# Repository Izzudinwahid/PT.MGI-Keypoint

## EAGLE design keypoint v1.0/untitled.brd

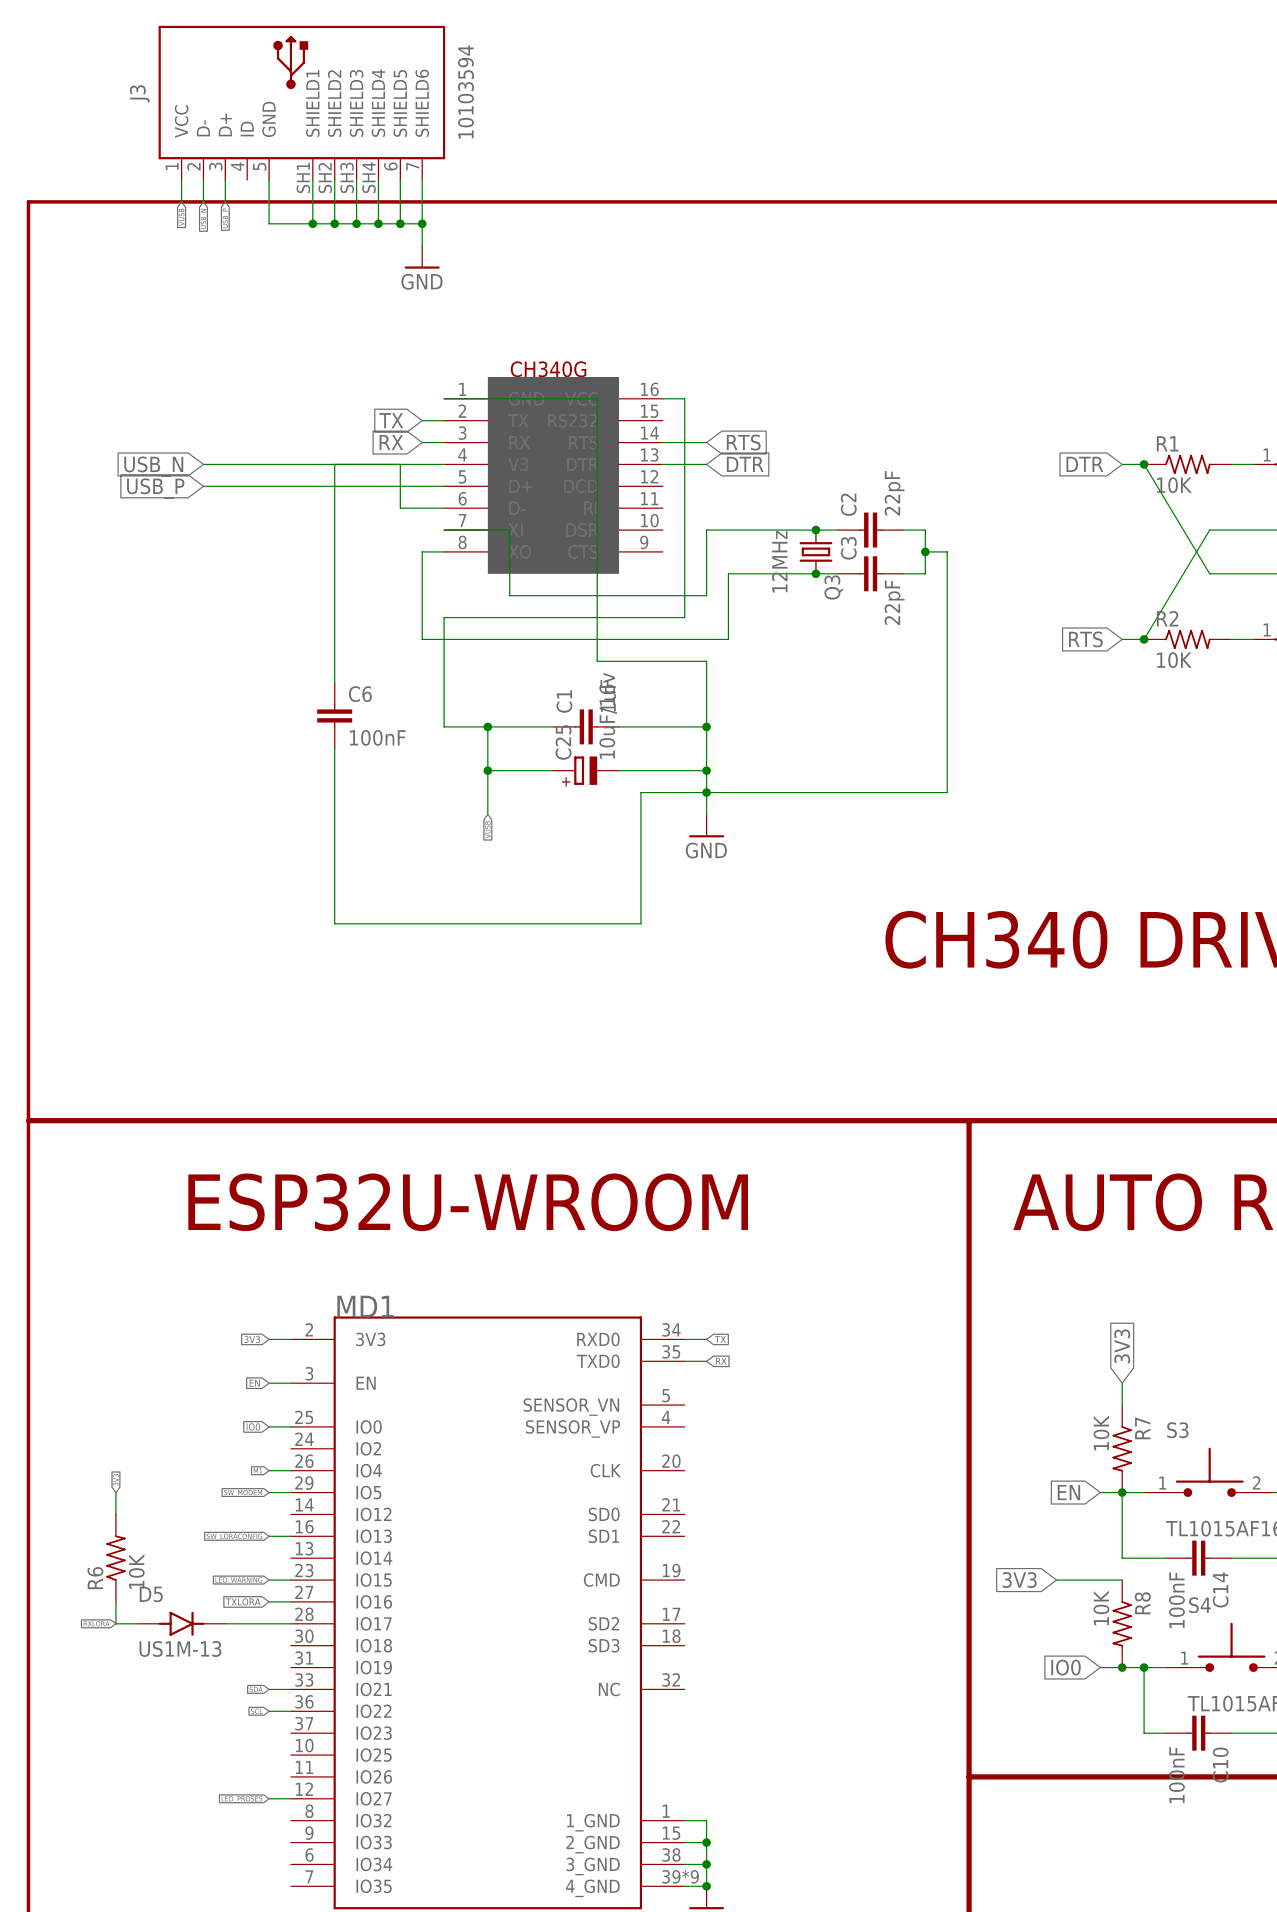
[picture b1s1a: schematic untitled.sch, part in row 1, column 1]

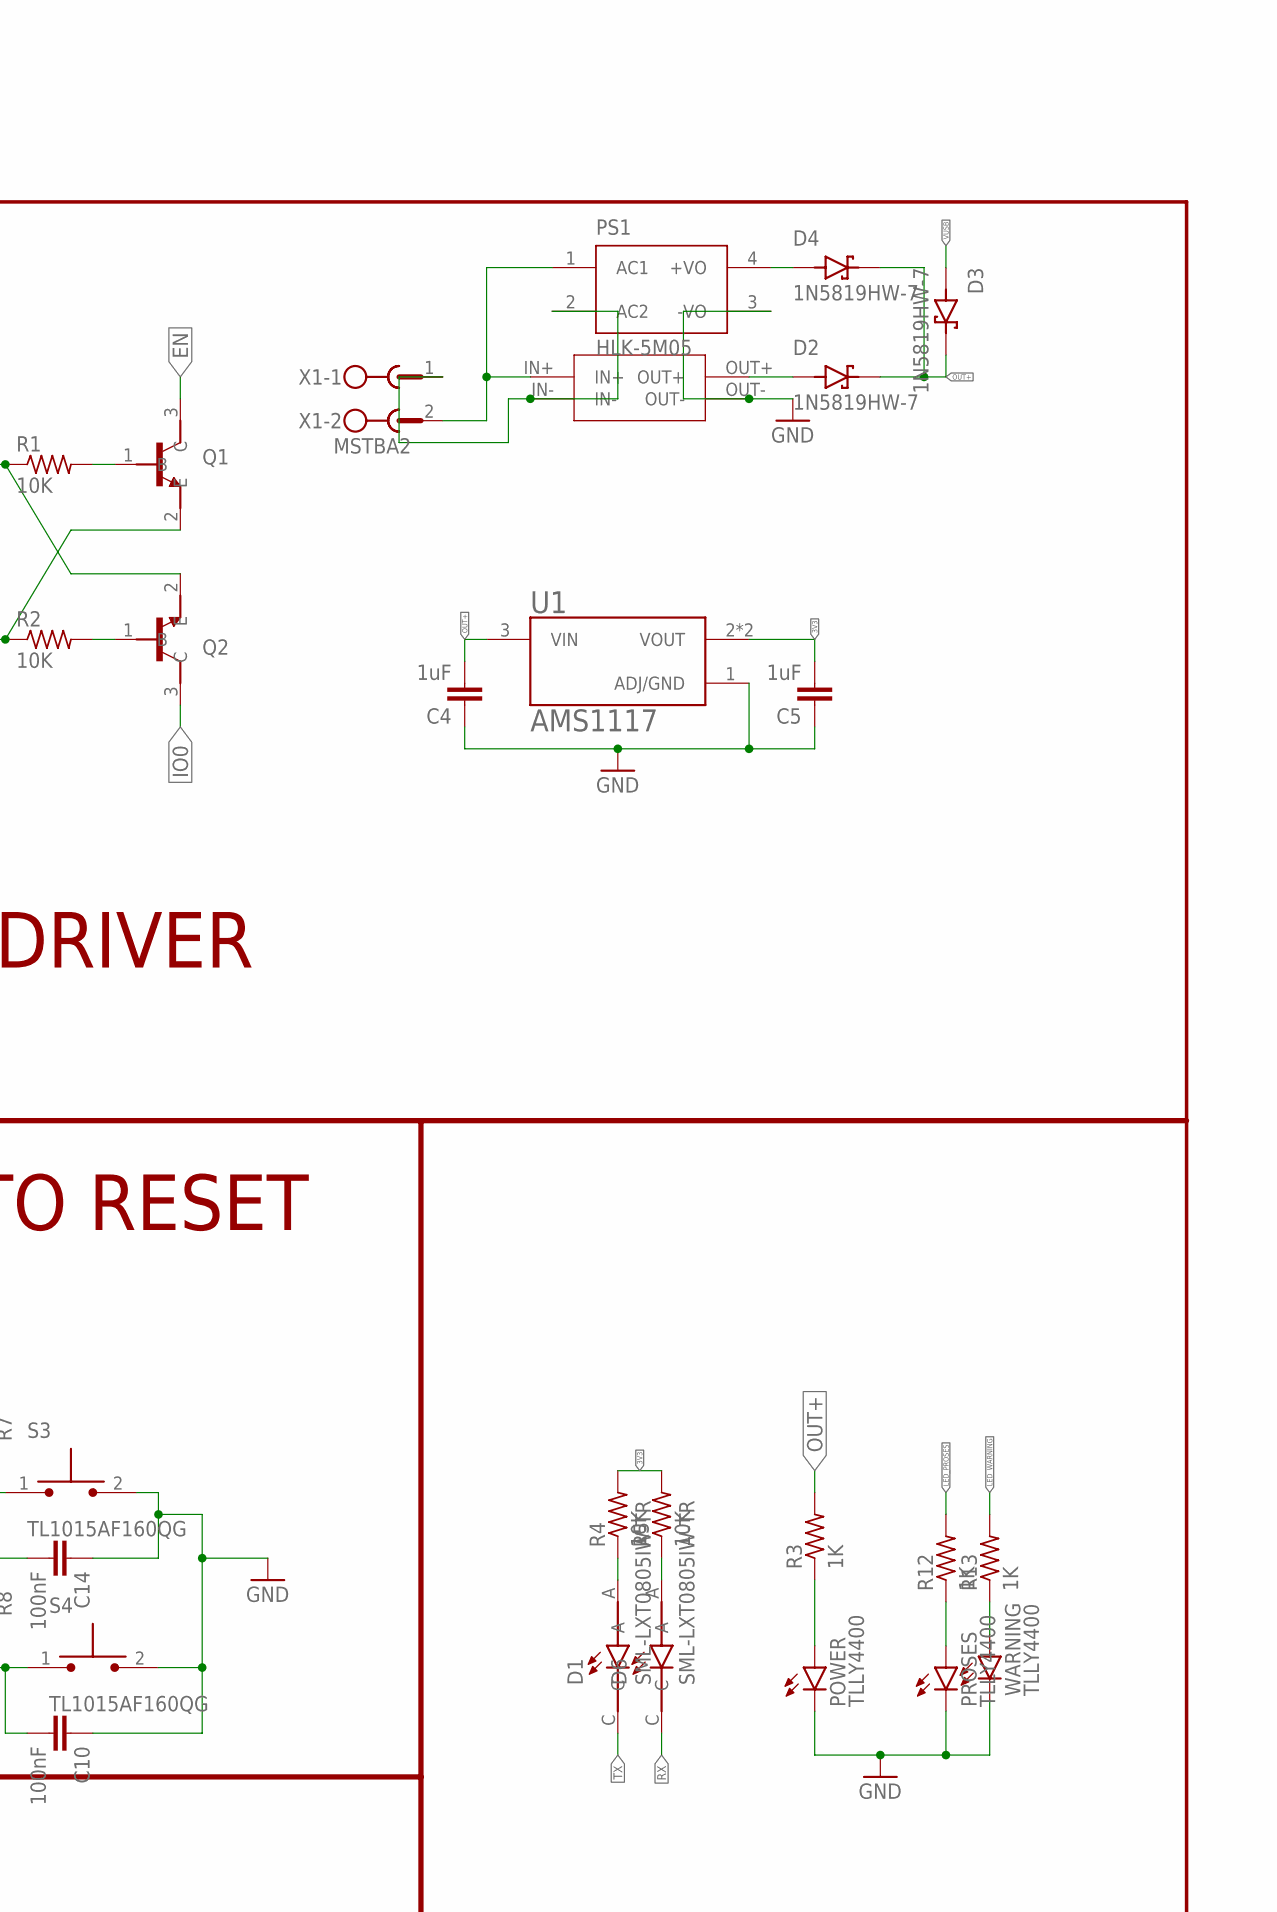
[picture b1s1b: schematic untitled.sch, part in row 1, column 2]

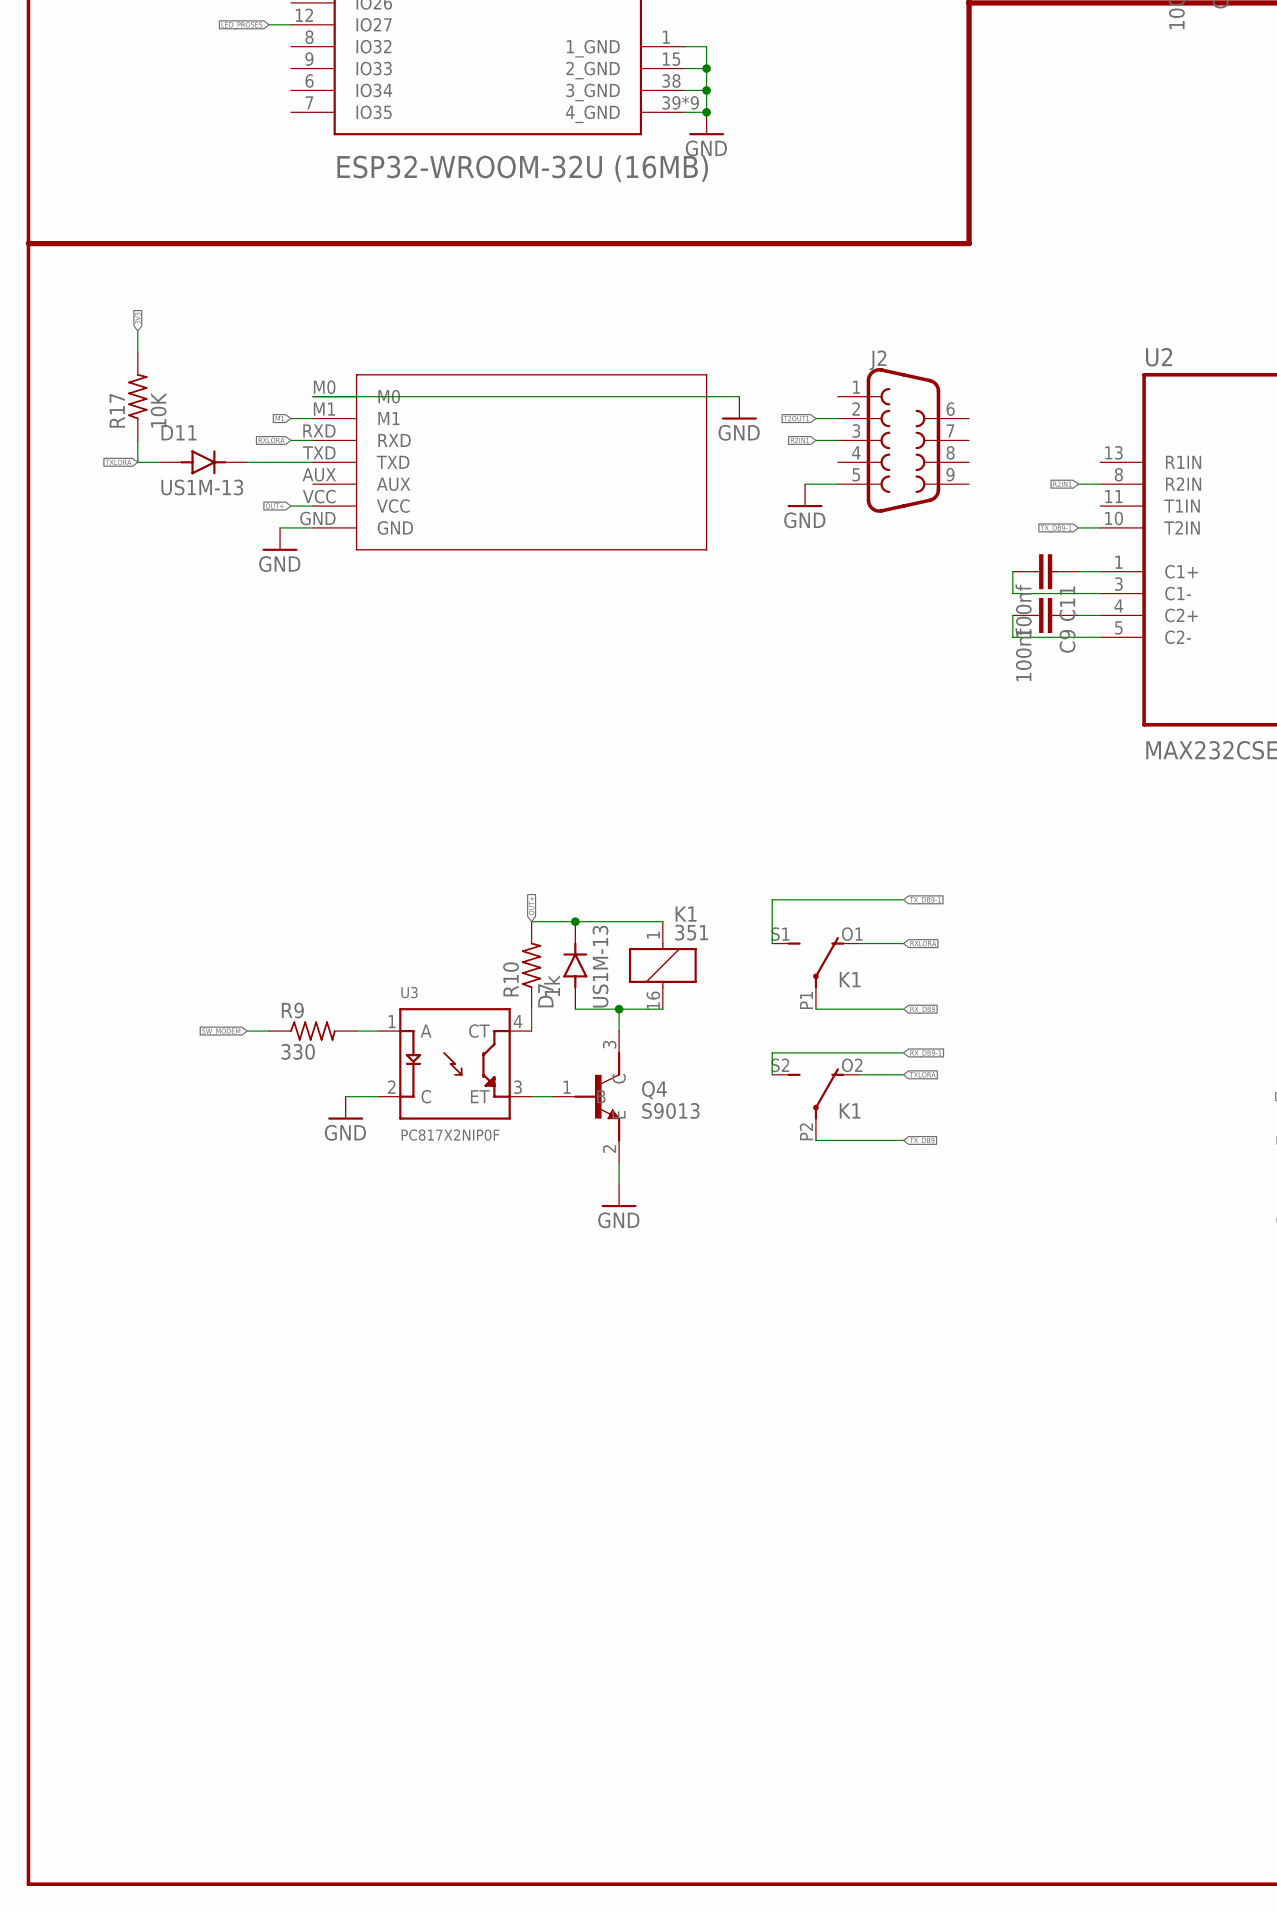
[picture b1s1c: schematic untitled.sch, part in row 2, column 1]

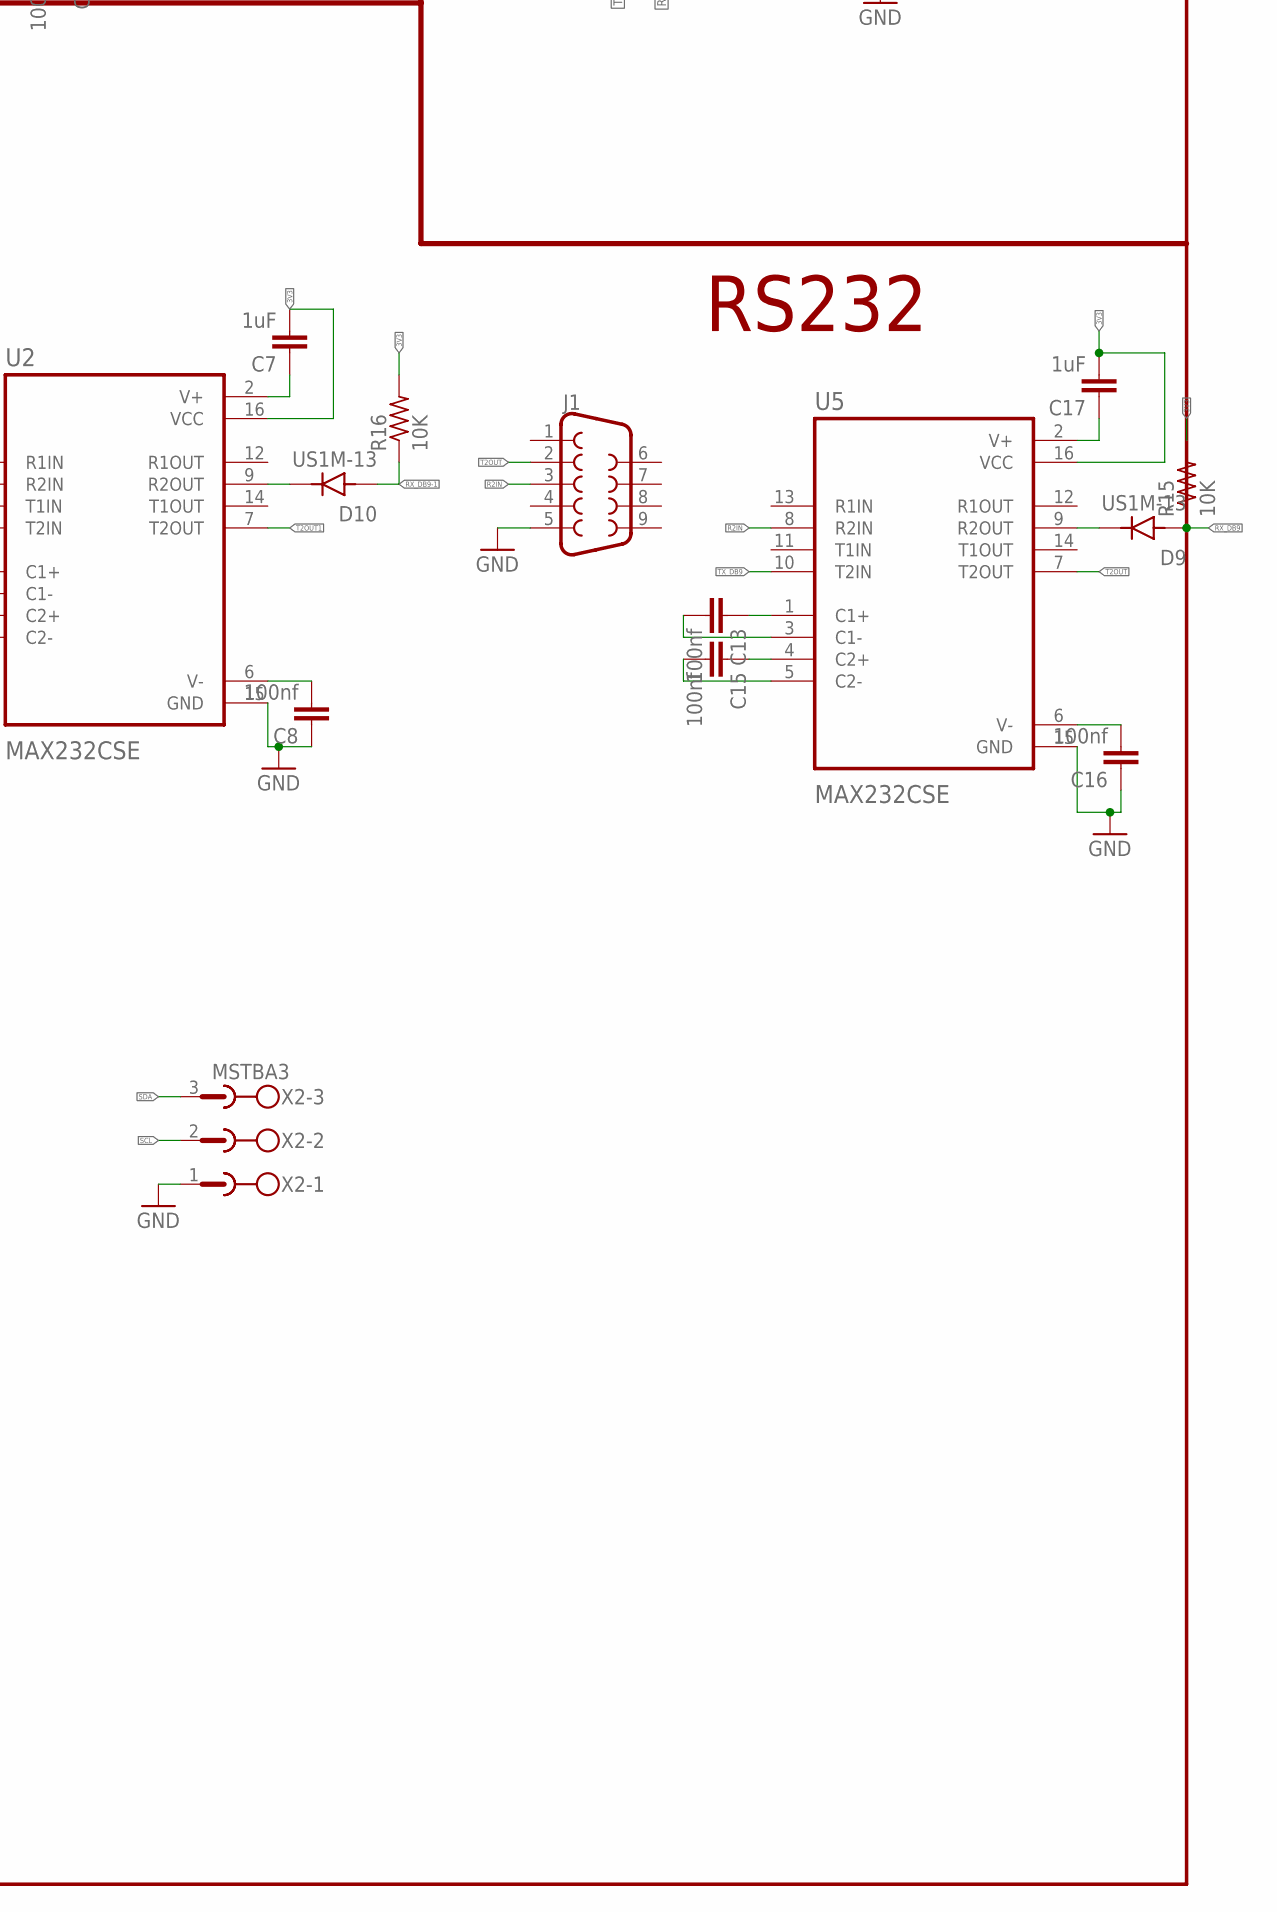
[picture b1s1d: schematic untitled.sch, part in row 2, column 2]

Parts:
C1, C4, C5: 1uF; C0805K
C2, C3: 22pF; C0805K
C6, C10, C14: 100nF; C0805K
C7, C17: 1uF; C0805
C8, C9, C11, C13, C15, C16: 100nf; C0805
C25: 10uF/16v; 153CLV-0505
D1, D6: SML-LXT0805IW-TR; LEDC2012X120N
D2, D3, D4: 1N5819HW-7; SOD3715X145N
D5, D7, D9, D10, D11: US1M-13; DIOM5226X240N
EBYTEE220-900T22D1: EBYTEE220-900T22D
J1, J2: DB9MALE; DB9_MALE
J3: 10103594
K1: 351
MD1: ESPRESSIF_SYSTEMS_ESP32-WROOM-32U_16MBESPRESSIF_S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; ESPRESSIF_SYSTEMS_ESP32-WROOM-32U_16MB_0
MINI1: MINI560
POWER: TLLY4400; LED3MM
PROSES: TLLY4400; LED3MM
PS1: HLK-5M05; CONV_HLK-5M05
Q1, Q2: MMBT3904; SOT95P240X120-3N
Q3: 12MHz; SM49
Q4: S9013; SOT95P240X120-3N
R1, R2, R4, R5, R6, R7, R8, R15, R16, R17: 10K; M0805
R3, R12, R13: 1K; M0805
R9: 330; M0805
R10: 1k; M0805
S3, S4: TL1015AF160QG; SW_TL1015AF160QG
U1: AMS1117; SOT229P700X180-4N
U2, U5: MAX232CSE; SOIC127P600X175-16N
U3: PC817X2NIP0F; SOT254P975X400-4N
U$2: CH340G; SOIC16
WARNING: TLLY4400; LED3MM
X1: MSTBA2
X2: MSTBA3

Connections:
3V3: C5.2, C7.2, C17.2, MD1.2 (3V3), R4.2, R5.2, R6.2, R7.1, R8.1, R15.2, R16.2, R17.2, U1.2 (VOUT), U1.4 (VOUT), U2.16 (VCC), U5.16 (VCC)
DTR: Q2.2 (E), R1.1, U$2.13 (DTR)
EN: C14.2, MD1.3 (EN), Q1.3 (C), R7.2, S3.1
GND: C1.2, C2.2, C3.2, C4.1, C5.1, C6.2, C8.1, C10.1, C14.1, C16.1, C25.-, EBYTEE220-900T22D1.GND, EBYTEE220-900T22D1.M0, J1.5, J2.5, J3.5 (GND), J3.6 (SHIELD5), J3.7 (SHIELD6), J3.SH1 (SHIELD1), J3.SH2 (SHIELD2), J3.SH3 (SHIELD3), J3.SH4 (SHIELD4), MD1.1 (1_GND), MD1.15 (2_GND), MD1.38 (3_GND), MD1.39 (4_GND), MD1.39-2 (4_GND), MD1.39-3 (4_GND), MD1.39-4 (4_GND), MD1.39-5 (4_GND), MD1.39-6 (4_GND), MD1.39-7 (4_GND), MD1.39-8 (4_GND), MD1.39-9 (4_GND), MINI1.OUT-, POWER.K (C), PROSES.K (C), PS1.3 (-VO), Q4.2 (E), S3.2, S4.2, U1.1 (ADJ/GND), U2.15 (GND), U3.2 (C), U5.15 (GND), U$2.1 (GND), WARNING.K (C), X2.1
IO0: C10.2, MD1.25 (IO0), Q2.3 (C), R8.2, S4.1
LED_PROSES: MD1.12 (IO27), R12.2
LED_WARNING: MD1.23 (IO15), R13.2
M1: EBYTEE220-900T22D1.M1, MD1.26 (IO4)
unnamed: C2.1, Q3.1, U$2.7 (XI)
unnamed: C3.1, Q3.2, U$2.8 (XO)
unnamed: POWER.A, R3.1
unnamed: Q1.1 (B), R1.2
unnamed: Q2.1 (B), R2.2
unnamed: MINI1.IN+, PS1.1 (AC1), X1.2
unnamed: C7.1, U2.2 (V+)
unnamed: D1.A, R4.1
unnamed: D6.A, R5.1
unnamed: C13.1, U5.1 (C1+)
unnamed: D2.A, MINI1.OUT+
unnamed: C6.1, U$2.4 (V3)
unnamed: D5.C (K), MD1.28 (IO17)
unnamed: C13.2, U5.3 (C1-)
unnamed: R9.2, U3.1 (A)
unnamed: R10.1, U3.4 (CT)
unnamed: C8.2, U2.6 (V-)
unnamed: Q4.1 (B), U3.3 (ET)
unnamed: C15.1, U5.4 (C2+)
unnamed: C9.1, U2.4 (C2+)
unnamed: C9.2, U2.5 (C2-)
unnamed: C11.2, U2.3 (C1-)
unnamed: C11.1, U2.1 (C1+)
unnamed: C15.2, U5.5 (C2-)
unnamed: PROSES.A, R12.1
unnamed: C17.1, U5.2 (V+)
unnamed: C16.2, U5.6 (V-)
unnamed: R13.1, WARNING.A
unnamed: D7.A, K1.16 (2), Q4.3 (C)
unnamed: MINI1.IN-, PS1.2 (AC2), X1.1
unnamed: D4.A, PS1.4 (+VO)
unnamed: D9.C (K), U5.9 (R2OUT)
unnamed: D10.C (K), U2.9 (R2OUT)
unnamed: D11.C (K), EBYTEE220-900T22D1.TXD
OUT+: C4.2, D2.C (K), D3.C (K), D4.C (K), D7.C (K), EBYTEE220-900T22D1.VCC, K1.1, R3.2, R10.2, U1.3 (VIN)
R2IN: J1.3, U5.8 (R2IN)
R2IN1: J2.3, U2.8 (R2IN)
RTS: Q1.2 (E), R2.1, U$2.14 (RTS)
RX: D6.C, MD1.35 (TXD0), U$2.3 (RX)
RXLORA: D5.A, EBYTEE220-900T22D1.RXD, K1.O1 (O), R6.1
RX_DB9: D9.A, K1.P1, R15.1
RX_DB9-1: D10.A, K1.S2 (S), R16.1
SCL: MD1.36 (IO22), X2.2
SDA: MD1.33 (IO21), X2.3
SW_LORACONFIG: MD1.16 (IO13)
SW_MODEM: MD1.29 (IO5), R9.1
T2OUT: J1.2, U5.7 (T2OUT)
T2OUT1: J2.2, U2.7 (T2OUT)
TX: D1.C, MD1.34 (RXD0), U$2.2 (TX)
TXLORA: D11.A, K1.O2 (O), MD1.27 (IO16), R17.1
TX_DB9: K1.P2, U5.10 (T2IN)
TX_DB9-1: K1.S1 (S), U2.10 (T2IN)
USB_N: J3.2 (D-), U$2.6 (D-)
USB_P: J3.3 (D+), U$2.5 (D+)
VUSB: C1.1, C25.+, D3.A, J3.1 (VCC), U$2.16 (VCC)

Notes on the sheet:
CH340 DRIVER
ESP32U-WROOM
AUTO RESET
RS232

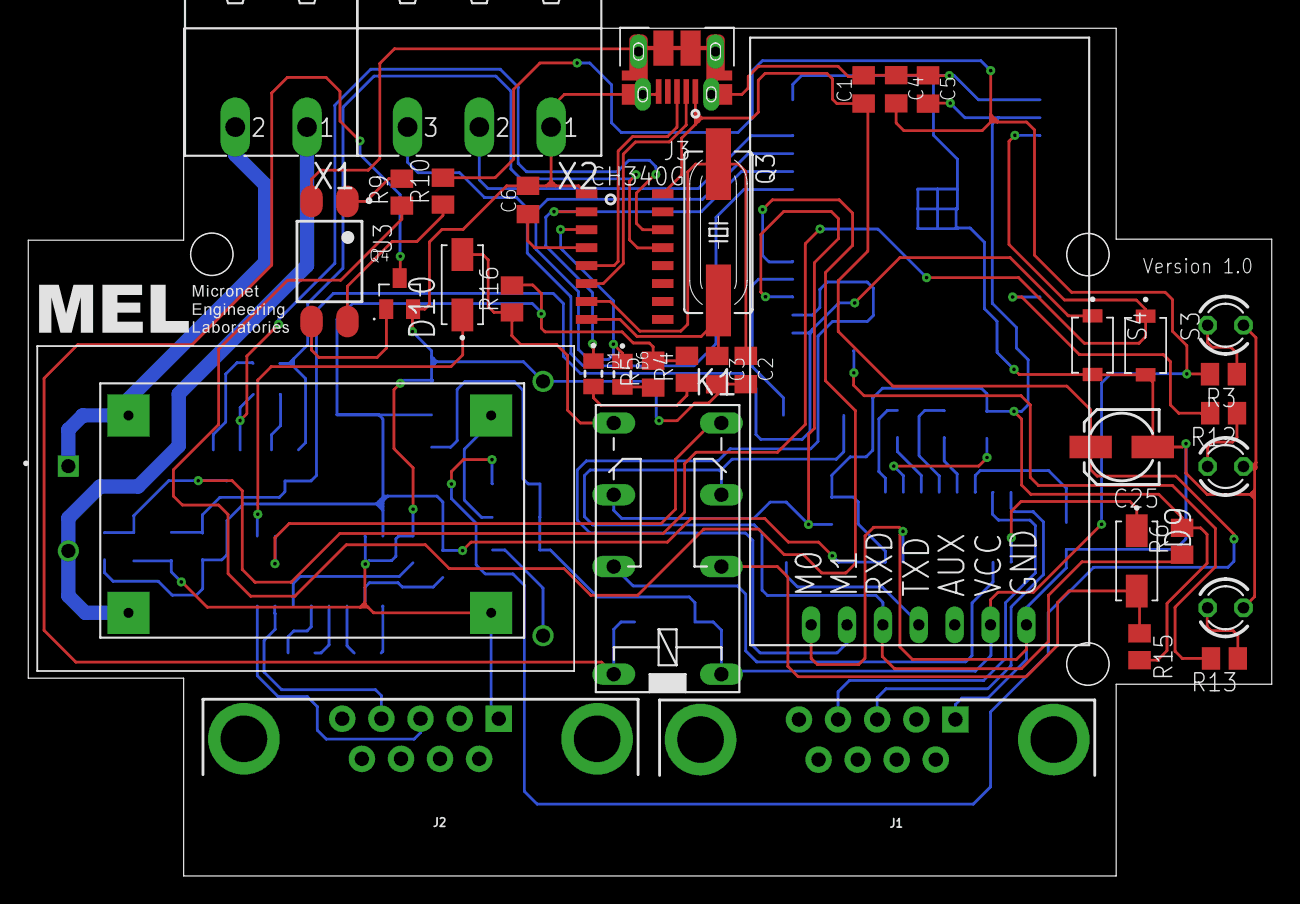
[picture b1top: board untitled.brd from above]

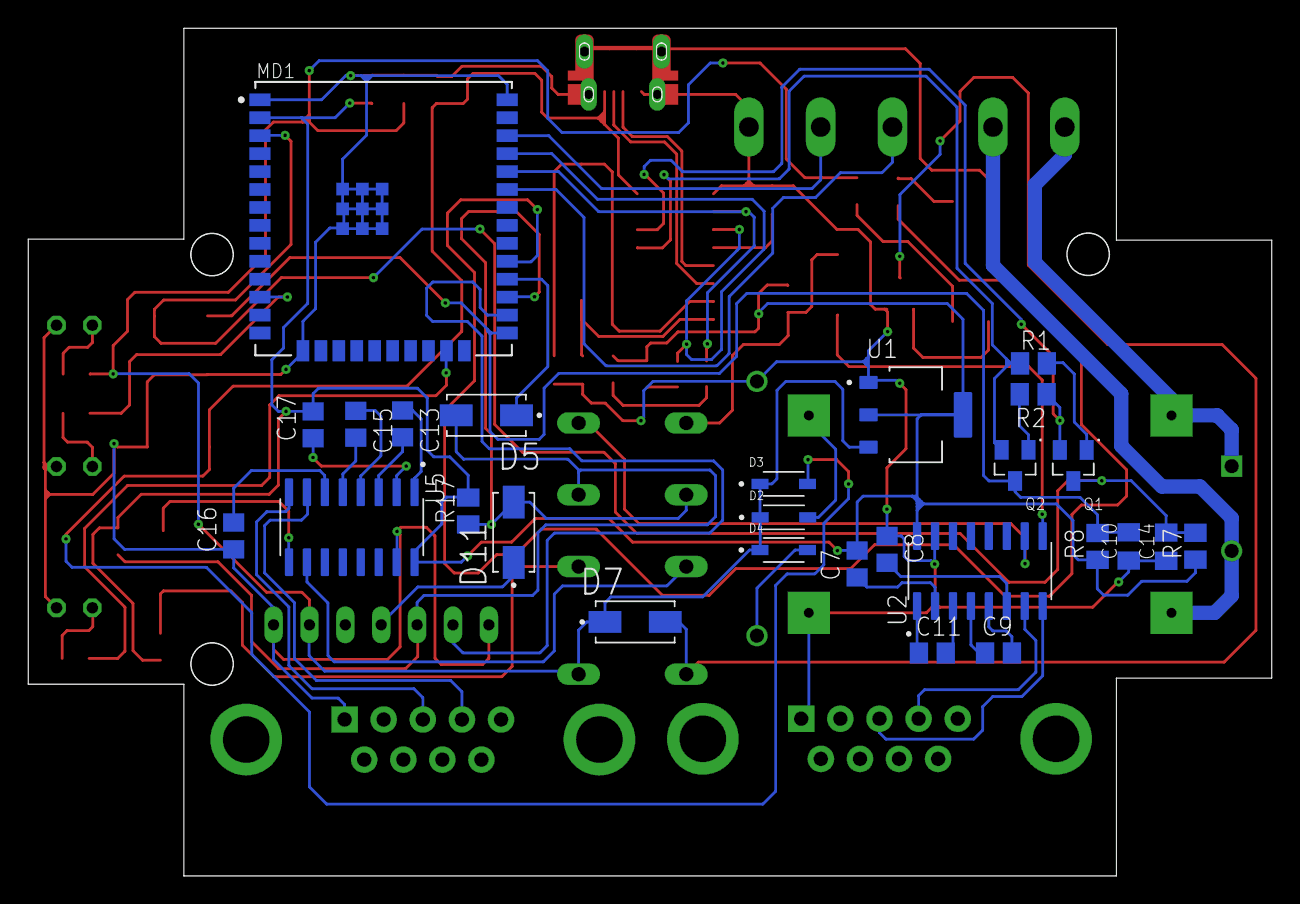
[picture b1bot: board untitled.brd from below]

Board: 2 copper layers, 88.0 x 60.0 mm, 66 parts (27 on the bottom side), 62 nets.

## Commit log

2023-06-06 PCB Keypoint v1.0
2023-06-13 fix PCB
2023-06-19 fix PCB versi 1.0
2023-06-20 fix PCB version 1.0
2023-08-15 fix v1.0

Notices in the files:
parts and their libraries:
SparkFun-Connectors: Licensing: Creative Commons ShareAlike 4.0 International - https://creativecommons.org/licenses/by-sa/4.0
